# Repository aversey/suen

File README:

This board is the first implementation of SUEN architecture.

SUEN archictecture was created by Nikita Orlov and Aleksey Veresov
for research and educational purposes.

Board schematic was created with KiCad program complex.

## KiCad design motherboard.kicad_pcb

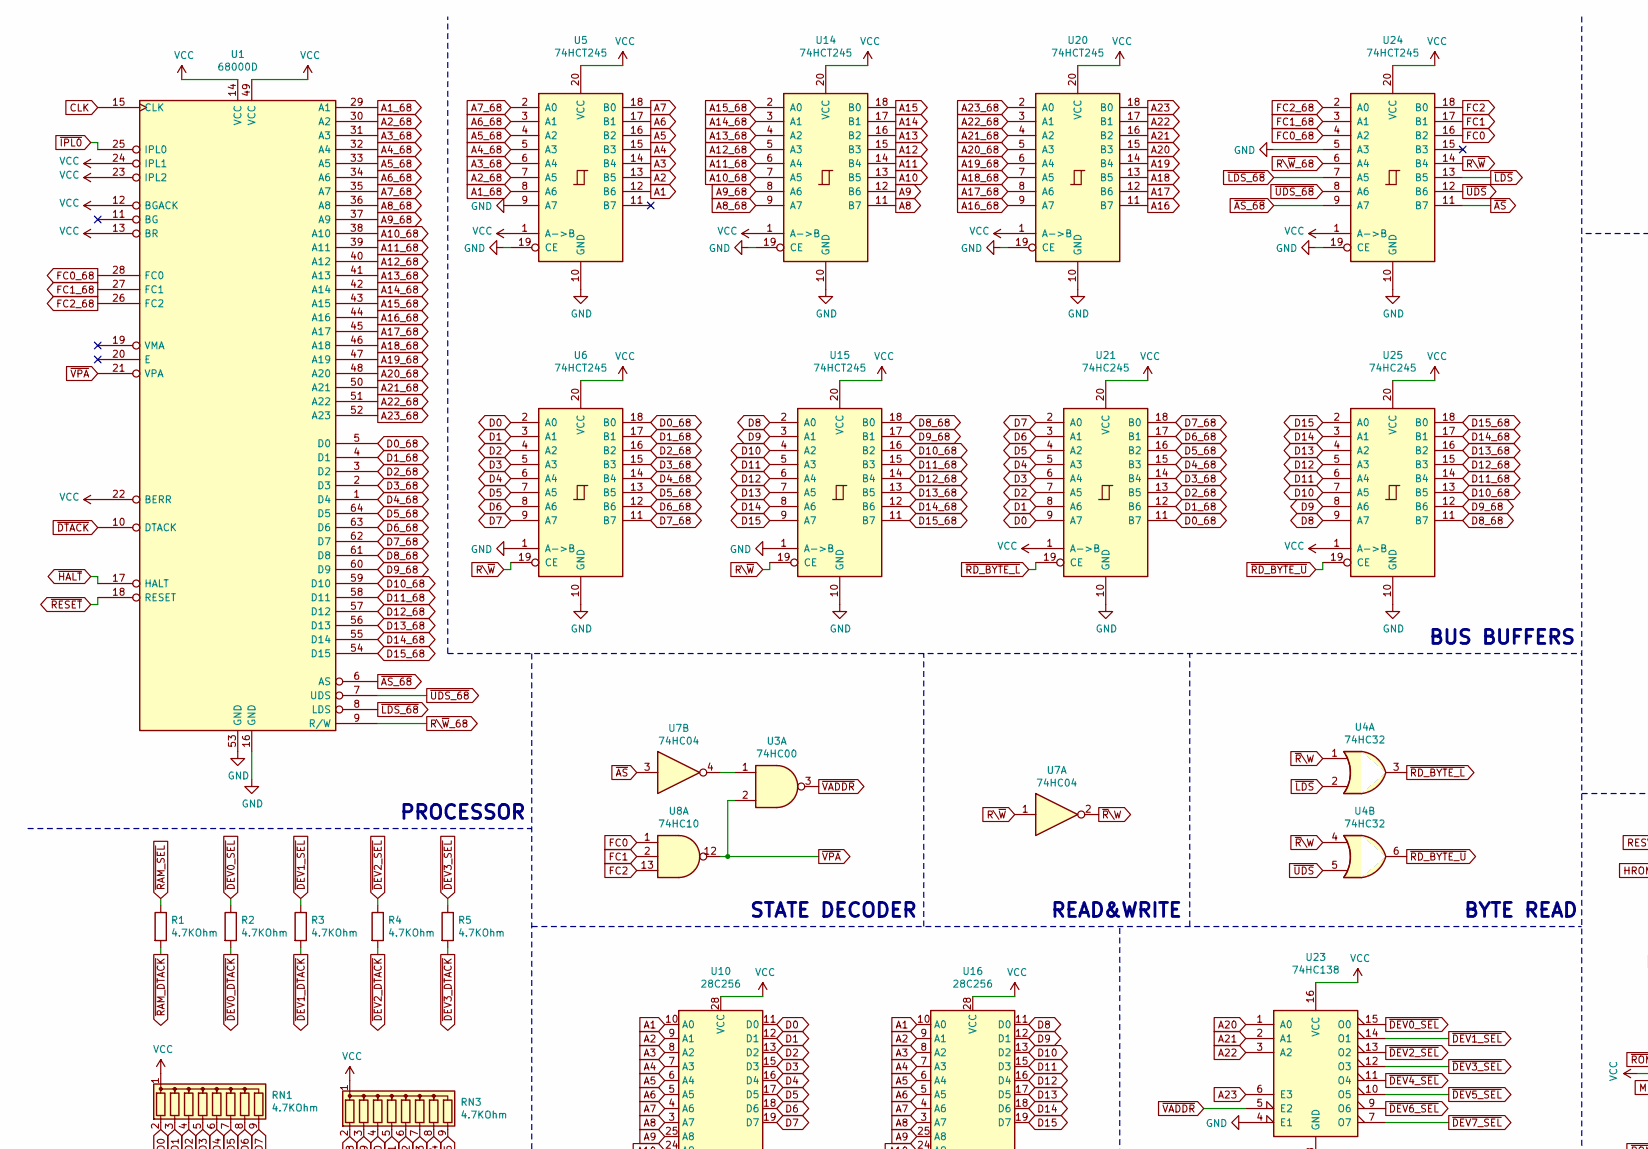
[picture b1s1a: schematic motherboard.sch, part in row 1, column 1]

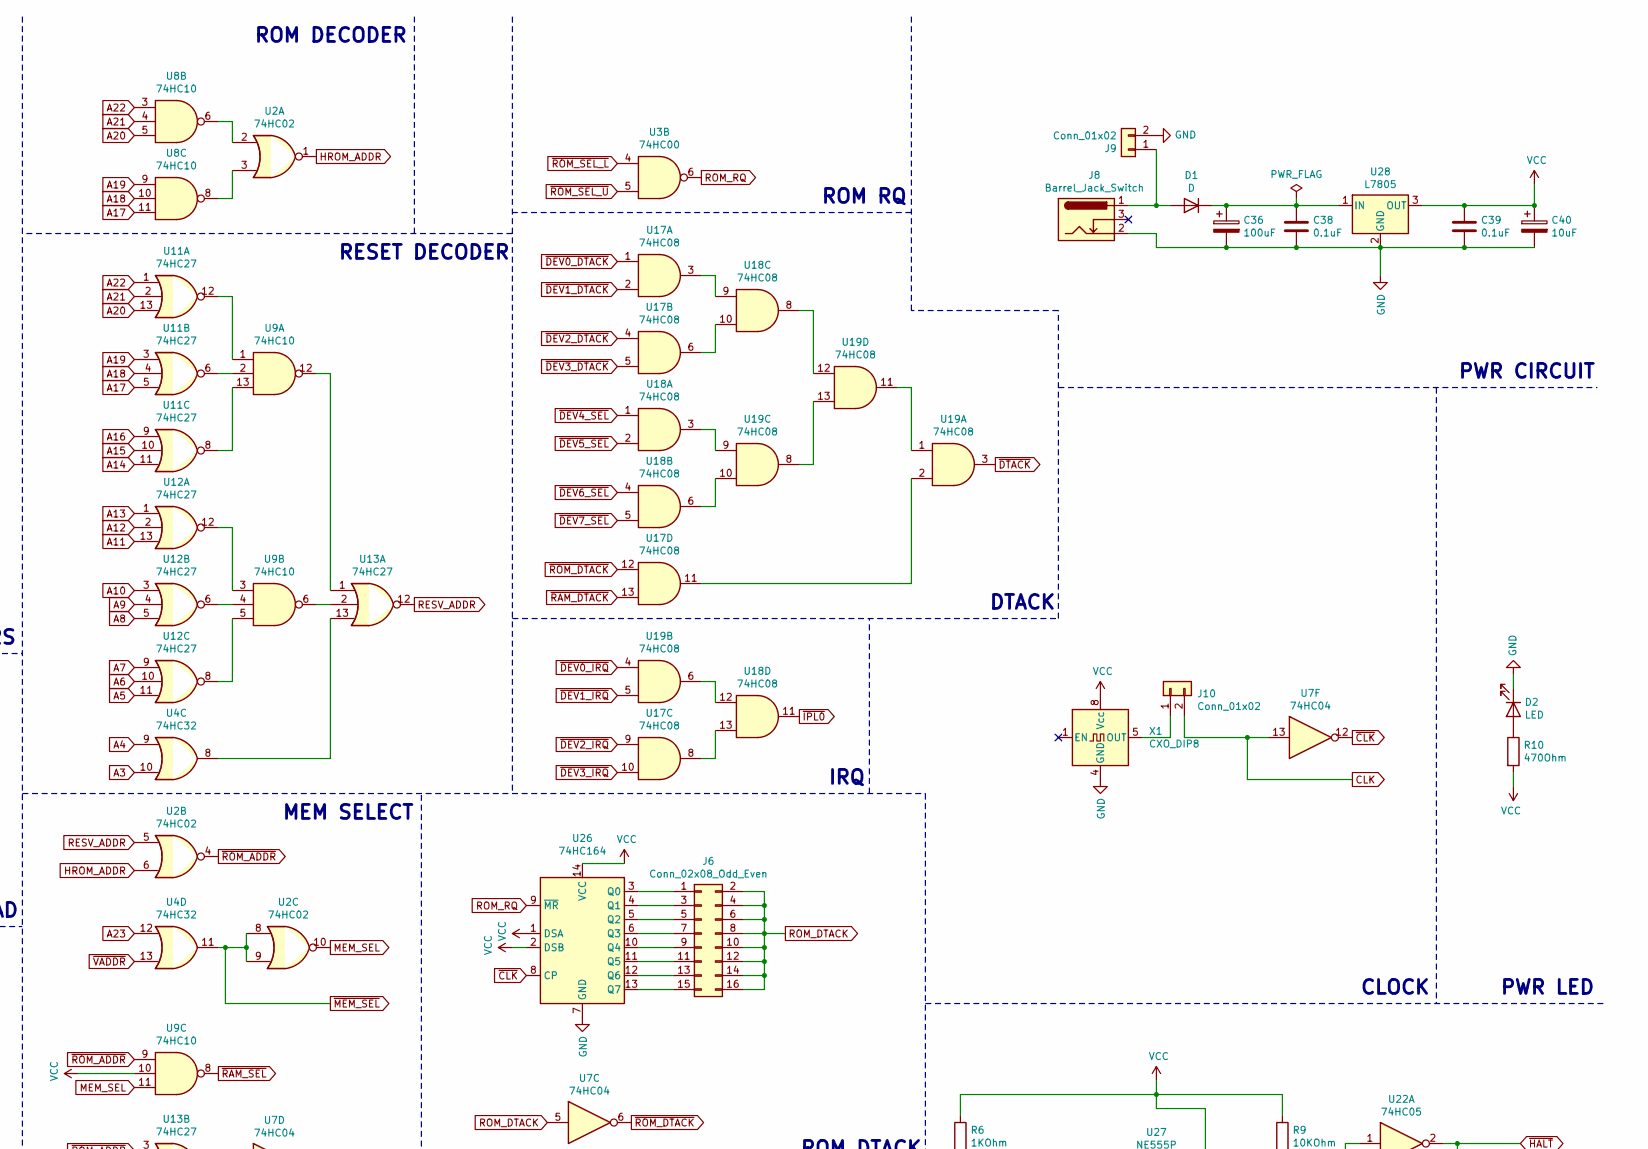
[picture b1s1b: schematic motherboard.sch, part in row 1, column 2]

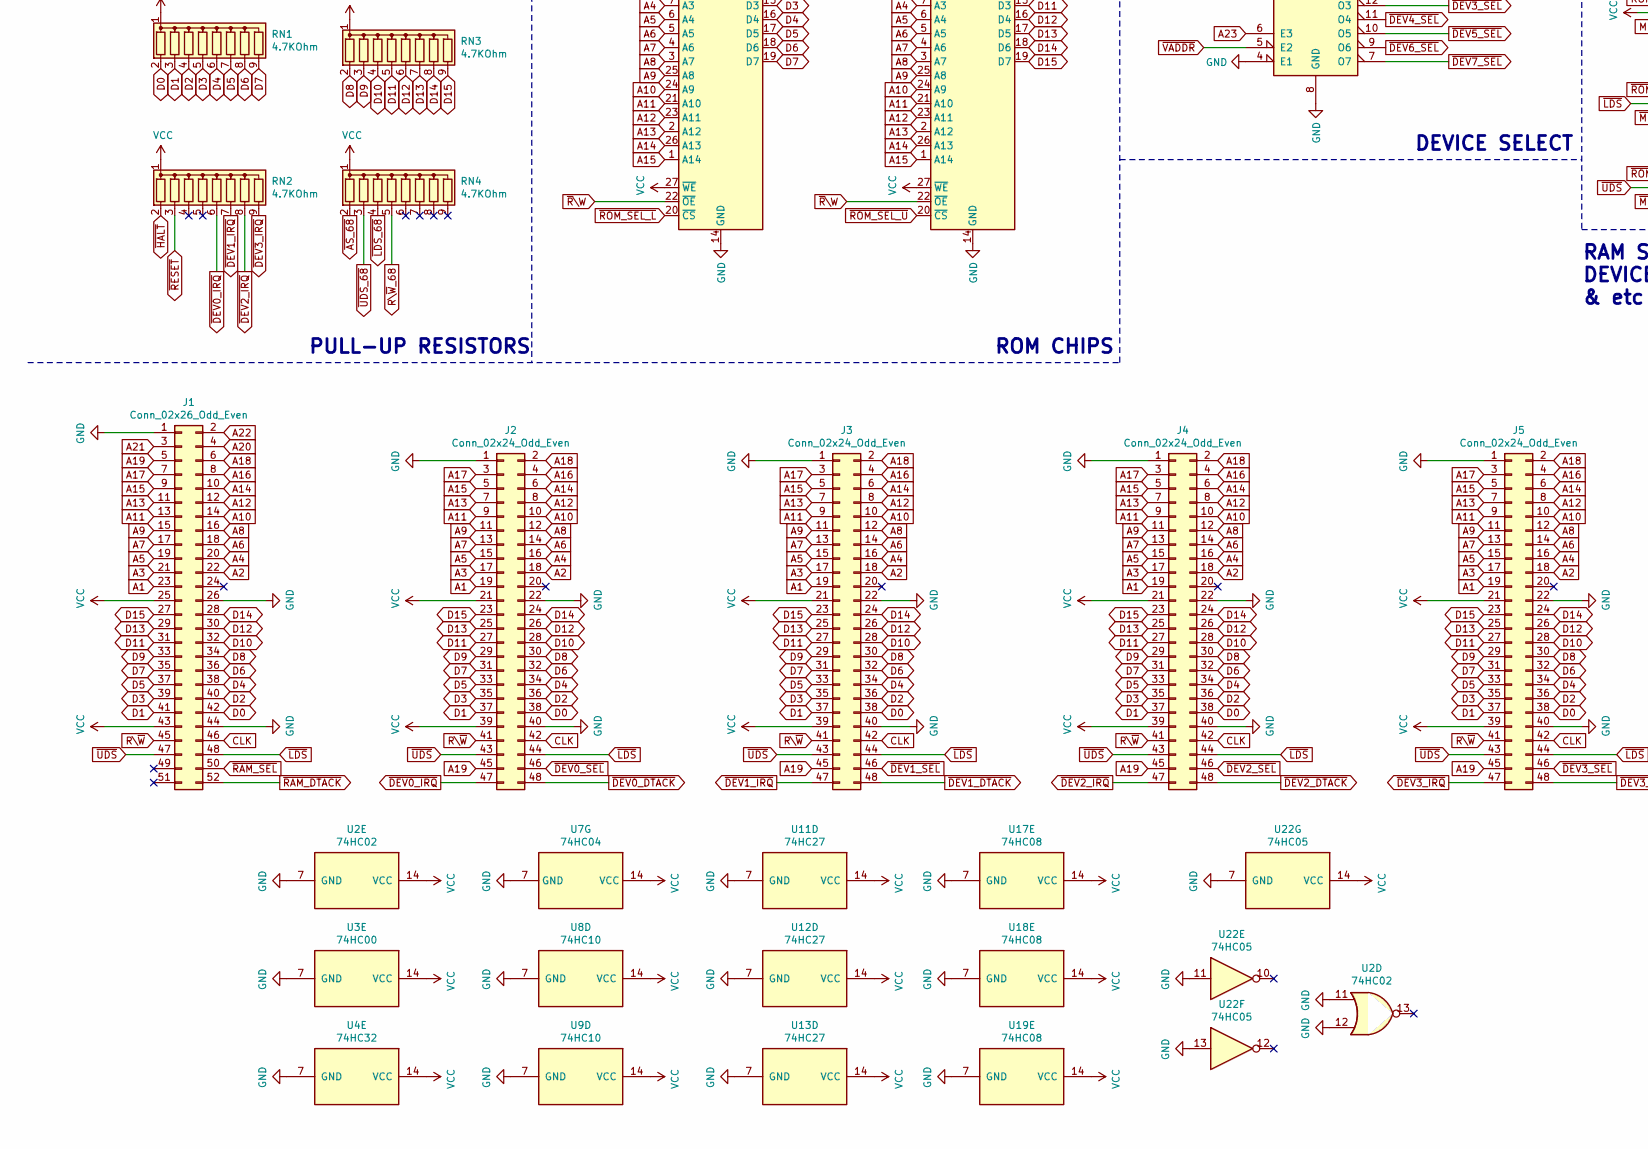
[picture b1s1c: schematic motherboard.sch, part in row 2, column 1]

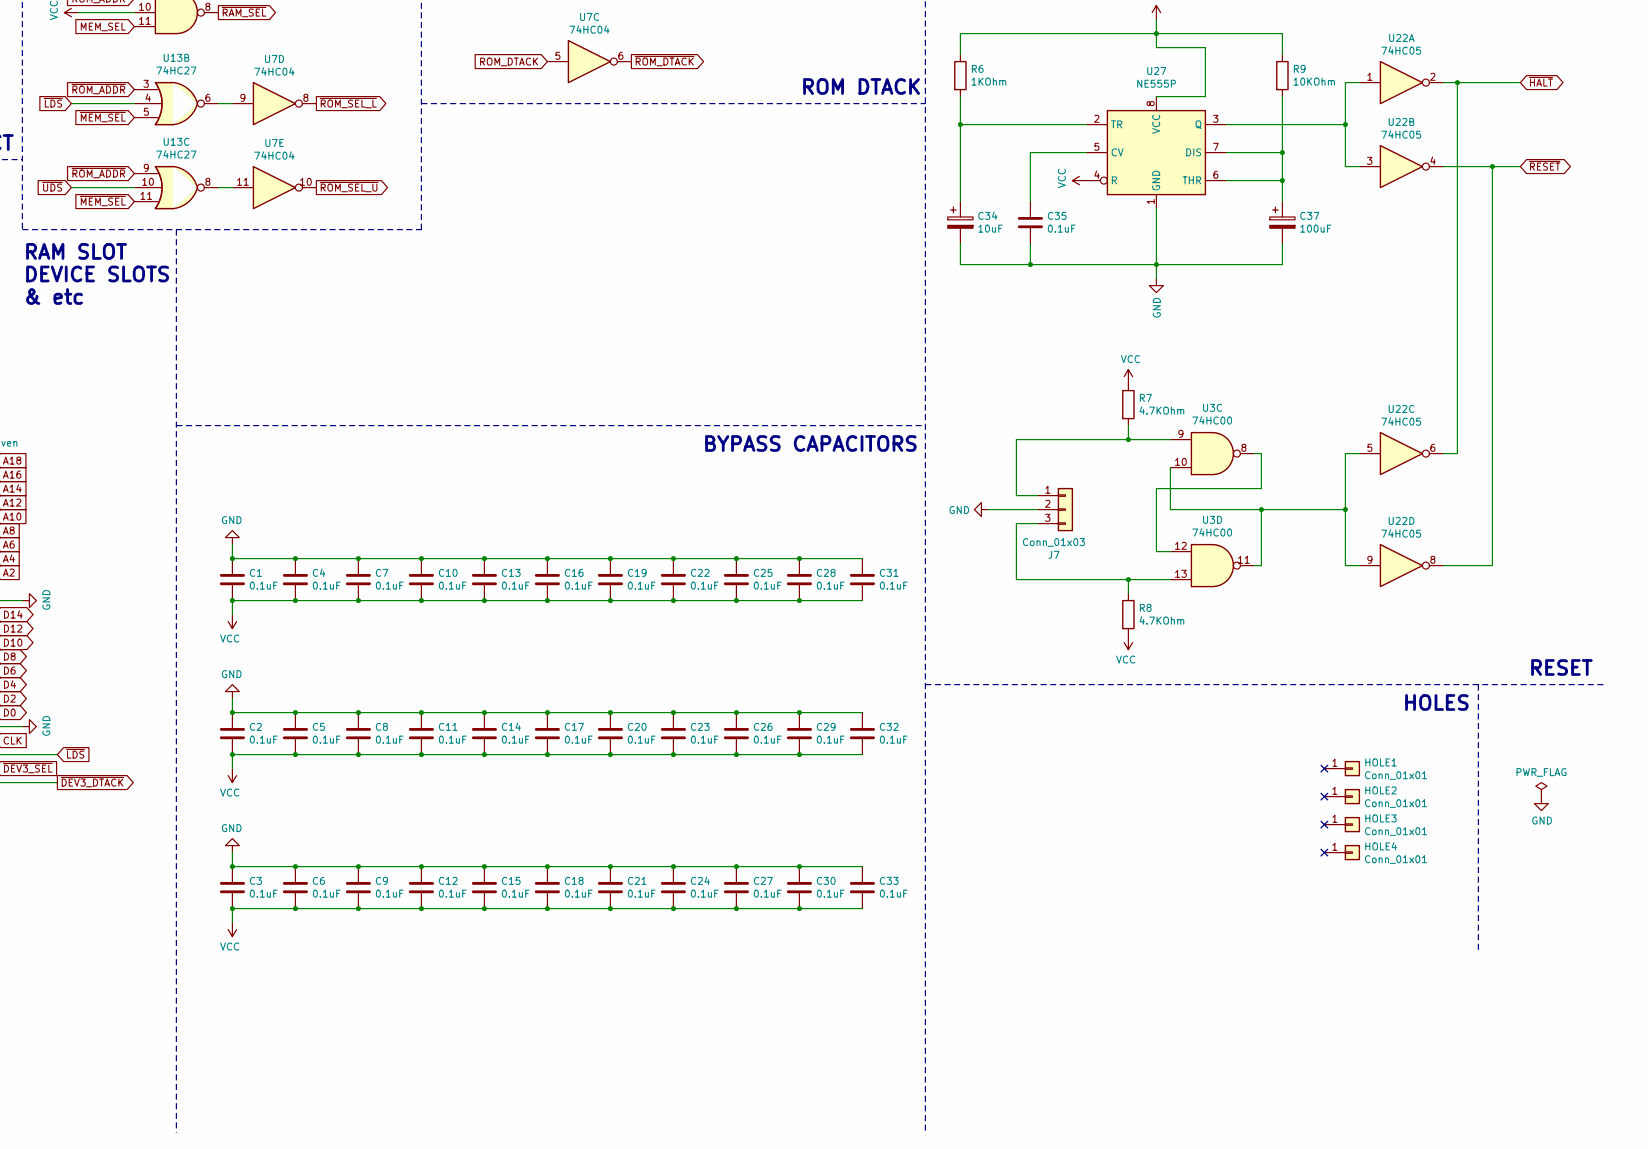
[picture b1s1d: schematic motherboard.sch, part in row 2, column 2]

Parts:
C1, C2, C3, C4, C5, C6, C7, C8, C9, C10, C11, C12, C13, C14, C15, C16, C17, C18, C19, C20, C21, C22, C23, C24, C25, C26, C27, C28, C29, C30, C31, C32, C33, C35, C38, C39: 0.1uF; C_Rect_L7.0mm_W4.5mm_P5.00mm
C34, C40: 10uF; CP_Radial_D4.0mm_P2.00mm
C36, C37: 100uF; CP_Radial_D5.0mm_P2.50mm
D1: D; D_DO-41_SOD81_P10.16mm_Horizontal
D2: LED; LED_D5.0mm
HOLE1, HOLE2, HOLE3, HOLE4: Conn_01x01; Hole
J1: Conn_02x26_Odd_Even; PinHeader_2x26_P2.54mm_Vertical
J2, J3, J4, J5: Conn_02x24_Odd_Even; PinHeader_2x24_P2.54mm_Vertical
J6: Conn_02x08_Odd_Even; PinHeader_2x08_P2.54mm_Vertical
J7: Conn_01x03; PinHeader_1x03_P2.54mm_Vertical
J8: Barrel_Jack_Switch; BarrelJack_Horizontal
J9, J10: Conn_01x02; PinHeader_1x02_P2.54mm_Vertical
R1, R2, R3, R4, R5, R7, R8: 4.7KOhm; R_Axial_DIN0414_L11.9mm_D4.5mm_P20.32mm_Horizontal
R6: 1KOhm; R_Axial_DIN0414_L11.9mm_D4.5mm_P20.32mm_Horizontal
R9: 10KOhm; R_Axial_DIN0414_L11.9mm_D4.5mm_P20.32mm_Horizontal
R10: 470Ohm; R_Axial_DIN0414_L11.9mm_D4.5mm_P20.32mm_Horizontal
RN1, RN2, RN3, RN4: 4.7KOhm; R_Array_SIP9
U1: 68000D; DIP-64_W22.86mm_Socket
U2: 74HC02; DIP-14_W7.62mm_Socket
U3: 74HC00; DIP-14_W7.62mm_Socket
U4: 74HC32; DIP-14_W7.62mm_Socket
U5, U6, U14, U15, U20, U24: 74HCT245; DIP-20_W7.62mm_Socket
U7: 74HC04; DIP-14_W7.62mm_Socket
U8, U9: 74HC10; DIP-14_W7.62mm_Socket
U10, U16: 28C256; DIP-28_W15.24mm_Socket
U11, U12, U13: 74HC27; DIP-14_W7.62mm_Socket
U17, U18, U19: 74HC08; DIP-14_W7.62mm_Socket
U21, U25: 74HC245; DIP-20_W7.62mm_Socket
U22: 74HC05; DIP-14_W7.62mm_Socket
U23: 74HC138; DIP-16_W7.62mm_Socket
U26: 74HC164; DIP-14_W7.62mm_Socket
U27: NE555P; DIP-8_W7.62mm_Socket
U28: L7805; TO-220-3_Horizontal_TabDown
X1: CXO_DIP8; Oscillator_DIP-8

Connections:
A1: J1.23, J2.19, J3.19, J4.19, J5.19, U5.12 (B6), U10.10 (A0), U16.10 (A0)
A1_68: U1.29 (A1), U5.8 (A6)
A2: J1.22, J2.18, J3.18, J4.18, J5.18, U5.13 (B5), U10.9 (A1), U16.9 (A1)
A2_68: U1.30 (A2), U5.7 (A5)
A3: J1.21, J2.17, J3.17, J4.17, J5.17, U4.10, U5.14 (B4), U10.8 (A2), U16.8 (A2)
A3_68: U1.31 (A3), U5.6 (A4)
A4: J1.20, J2.16, J3.16, J4.16, J5.16, U4.9, U5.15 (B3), U10.7 (A3), U16.7 (A3)
A4_68: U1.32 (A4), U5.5 (A3)
A5: J1.19, J2.15, J3.15, J4.15, J5.15, U5.16 (B2), U10.6 (A4), U12.11, U16.6 (A4)
A5_68: U1.33 (A5), U5.4 (A2)
A6: J1.18, J2.14, J3.14, J4.14, J5.14, U5.17 (B1), U10.5 (A5), U12.10, U16.5 (A5)
A6_68: U1.34 (A6), U5.3 (A1)
A7: J1.17, J2.13, J3.13, J4.13, J5.13, U5.18 (B0), U10.4 (A6), U12.9, U16.4 (A6)
A7_68: U1.35 (A7), U5.2 (A0)
A8: J1.16, J2.12, J3.12, J4.12, J5.12, U10.3 (A7), U12.5, U14.11 (B7), U16.3 (A7)
A8_68: U1.36 (A8), U14.9 (A7)
A9: J1.15, J2.11, J3.11, J4.11, J5.11, U10.25 (A8), U12.4, U14.12 (B6), U16.25 (A8)
A9_68: U1.37 (A9), U14.8 (A6)
A10: J1.14, J2.10, J3.10, J4.10, J5.10, U10.24 (A9), U12.3, U14.13 (B5), U16.24 (A9)
A10_68: U1.38 (A10), U14.7 (A5)
A11: J1.13, J2.9, J3.9, J4.9, J5.9, U10.21 (A10), U12.13, U14.14 (B4), U16.21 (A10)
A11_68: U1.39 (A11), U14.6 (A4)
A12: J1.12, J2.8, J3.8, J4.8, J5.8, U10.23 (A11), U12.2, U14.15 (B3), U16.23 (A11)
A12_68: U1.40 (A12), U14.5 (A3)
A13: J1.11, J2.7, J3.7, J4.7, J5.7, U10.2 (A12), U12.1, U14.16 (B2), U16.2 (A12)
A13_68: U1.41 (A13), U14.4 (A2)
A14: J1.10, J2.6, J3.6, J4.6, J5.6, U10.26 (A13), U11.11, U14.17 (B1), U16.26 (A13)
A14_68: U1.42 (A14), U14.3 (A1)
A15: J1.9, J2.5, J3.5, J4.5, J5.5, U10.1 (A14), U11.10, U14.18 (B0), U16.1 (A14)
A15_68: U1.43 (A15), U14.2 (A0)
A16: J1.8, J2.4, J3.4, J4.4, J5.4, U11.9, U20.11 (B7)
A16_68: U1.44 (A16), U20.9 (A7)
A17: J1.7, J2.3, J3.3, J4.3, J5.3, U8.11, U11.5, U20.12 (B6)
A17_68: U1.45 (A17), U20.8 (A6)
A18: J1.6, J2.2, J3.2, J4.2, J5.2, U8.10, U11.4, U20.13 (B5)
A18_68: U1.46 (A18), U20.7 (A5)
A19: J1.5, J2.45, J3.45, J4.45, J5.45, U8.9, U11.3, U20.14 (B4)
A19_68: U1.47 (A19), U20.6 (A4)
A20: J1.4, U8.5, U11.13, U20.15 (B3), U23.1 (A0)
A20_68: U1.48 (A20), U20.5 (A3)
A21: J1.3, U8.4, U11.2, U20.16 (B2), U23.2 (A1)
A21_68: U1.50 (A21), U20.4 (A2)
A22: J1.2, U8.3, U11.1, U20.17 (B1), U23.3 (A2)
A22_68: U1.51 (A22), U20.3 (A1)
A23: U4.12, U20.18 (B0), U23.6 (E3)
A23_68: U1.52 (A23), U20.2 (A0)
CLK: J1.46, J2.42, J3.42, J4.42, J5.42, J10.2, U1.15 (CLK), U7.13
D0: J1.42, J2.38, J3.38, J4.38, J5.38, RN1.2 (R1), U6.2 (A0), U10.11 (D0), U21.9 (A7)
D0_68: U1.5 (D0), U6.18 (B0), U21.11 (B7)
D1: J1.41, J2.37, J3.37, J4.37, J5.37, RN1.3 (R2), U6.3 (A1), U10.12 (D1), U21.8 (A6)
D1_68: U1.4 (D1), U6.17 (B1), U21.12 (B6)
D2: J1.40, J2.36, J3.36, J4.36, J5.36, RN1.4 (R3), U6.4 (A2), U10.13 (D2), U21.7 (A5)
D2_68: U1.3 (D2), U6.16 (B2), U21.13 (B5)
D3: J1.39, J2.35, J3.35, J4.35, J5.35, RN1.5 (R4), U6.5 (A3), U10.15 (D3), U21.6 (A4)
D3_68: U1.2 (D3), U6.15 (B3), U21.14 (B4)
D4: J1.38, J2.34, J3.34, J4.34, J5.34, RN1.6 (R5), U6.6 (A4), U10.16 (D4), U21.5 (A3)
D4_68: U1.1 (D4), U6.14 (B4), U21.15 (B3)
D5: J1.37, J2.33, J3.33, J4.33, J5.33, RN1.7 (R6), U6.7 (A5), U10.17 (D5), U21.4 (A2)
D5_68: U1.64 (D5), U6.13 (B5), U21.16 (B2)
D6: J1.36, J2.32, J3.32, J4.32, J5.32, RN1.8 (R7), U6.8 (A6), U10.18 (D6), U21.3 (A1)
D6_68: U1.63 (D6), U6.12 (B6), U21.17 (B1)
D7: J1.35, J2.31, J3.31, J4.31, J5.31, RN1.9 (R8), U6.9 (A7), U10.19 (D7), U21.2 (A0)
D7_68: U1.62 (D7), U6.11 (B7), U21.18 (B0)
D8: J1.34, J2.30, J3.30, J4.30, J5.30, RN3.2 (R1), U15.2 (A0), U16.11 (D0), U25.9 (A7)
D8_68: U1.61 (D8), U15.18 (B0), U25.11 (B7)
D9: J1.33, J2.29, J3.29, J4.29, J5.29, RN3.3 (R2), U15.3 (A1), U16.12 (D1), U25.8 (A6)
D9_68: U1.60 (D9), U15.17 (B1), U25.12 (B6)
D10: J1.32, J2.28, J3.28, J4.28, J5.28, RN3.4 (R3), U15.4 (A2), U16.13 (D2), U25.7 (A5)
D10_68: U1.59 (D10), U15.16 (B2), U25.13 (B5)
D11: J1.31, J2.27, J3.27, J4.27, J5.27, RN3.5 (R4), U15.5 (A3), U16.15 (D3), U25.6 (A4)
D11_68: U1.58 (D11), U15.15 (B3), U25.14 (B4)
D12: J1.30, J2.26, J3.26, J4.26, J5.26, RN3.6 (R5), U15.6 (A4), U16.16 (D4), U25.5 (A3)
D12_68: U1.57 (D12), U15.14 (B4), U25.15 (B3)
D13: J1.29, J2.25, J3.25, J4.25, J5.25, RN3.7 (R6), U15.7 (A5), U16.17 (D5), U25.4 (A2)
D13_68: U1.56 (D13), U15.13 (B5), U25.16 (B2)
D14: J1.28, J2.24, J3.24, J4.24, J5.24, RN3.8 (R7), U15.8 (A6), U16.18 (D6), U25.3 (A1)
D14_68: U1.55 (D14), U15.12 (B6), U25.17 (B1)
D15: J1.27, J2.23, J3.23, J4.23, J5.23, RN3.9 (R8), U15.9 (A7), U16.19 (D7), U25.2 (A0)
D15_68: U1.54 (D15), U15.11 (B7), U25.18 (B0)
FC0: U8.1, U24.16 (B2)
FC0_68: U1.28 (FC0), U24.4 (A2)
FC1: U8.2, U24.17 (B1)
FC1_68: U1.27 (FC1), U24.3 (A1)
FC2: U8.13, U24.18 (B0)
FC2_68: U1.26 (FC2), U24.2 (A0)
GND: C1.1, C2.1, C3.1, C4.1, C5.1, C6.1, C7.1, C8.1, C9.1, C10.1, C11.1, C12.1, C13.1, C14.1, C15.1, C16.1, C17.1, C18.1, C19.1, C20.1, C21.1, C22.1, C23.1, C24.1, C25.1, C26.1, C27.1, C28.1, C29.1, C30.1, C31.1, C32.1, C33.1, C34.2, C35.2, C36.2, C37.2, C38.2, C39.2, C40.2, D2.1 (K), J1.1, J1.26, J1.44, J2.1, J2.22, J2.40, J3.1, J3.22, J3.40, J4.1, J4.22, J4.40, J5.1, J5.22, J5.40, J7.2, J8.2, J9.2, U1.16 (GND), U1.53 (GND), U2.7 (GND), U2.11, U2.12, U3.7 (GND), U4.7 (GND), U5.9 (A7), U5.10 (GND), U5.19 (CE), U6.1 (A->B), U6.10 (GND), U7.7 (GND), U8.7 (GND), U9.7 (GND), U10.14 (GND), U11.7 (GND), U12.7 (GND), U13.7 (GND), U14.10 (GND), U14.19 (CE), U15.1 (A->B), U15.10 (GND), U16.14 (GND), U17.7 (GND), U18.7 (GND), U19.7 (GND), U20.10 (GND), U20.19 (CE), U21.10 (GND), U22.7 (GND), U22.11, U22.13, U23.4 (E1), U23.8 (GND), U24.5 (A3), U24.10 (GND), U24.19 (CE), U25.10 (GND), U26.7 (GND), U27.1 (GND), U28.2 (GND), X1.4 (GND)
HROM_ADDR: U2.1, U2.6
MEM_SEL: U2.10, U9.11
unnamed: C34.1, R6.2, U27.2 (TR)
unnamed: C35.1, U27.5 (CV)
unnamed: C36.1, C38.1, D1.1 (K), U28.1 (IN)
unnamed: C37.1, R9.2, U27.6 (THR), U27.7 (DIS)
unnamed: D1.2 (A), J8.1, J9.1
unnamed: D2.2 (A), R10.1
unnamed: J6.1, U26.3 (Q0)
unnamed: J6.3, U26.4 (Q1)
unnamed: J6.5, U26.5 (Q2)
unnamed: J6.7, U26.6 (Q3)
unnamed: J6.9, U26.10 (Q4)
unnamed: J6.11, U26.11 (Q5)
unnamed: J6.13, U26.12 (Q6)
unnamed: J6.15, U26.13 (Q7)
unnamed: J7.1, R7.2, U3.9
unnamed: J7.3, R8.1, U3.13
unnamed: J10.1, X1.5 (OUT)
unnamed: U2.2, U8.6
unnamed: U2.3, U8.8
unnamed: U3.1, U7.4
unnamed: U3.8, U3.12
unnamed: U9.2, U11.6
unnamed: U9.13, U11.8
unnamed: U9.1, U11.12
unnamed: U9.4, U12.6
unnamed: U9.5, U12.8
unnamed: U9.3, U12.12
unnamed: U9.12, U13.1
unnamed: U9.6, U13.2
unnamed: U7.9, U13.6
unnamed: U7.11, U13.8
unnamed: U4.8, U13.13
unnamed: U17.3, U18.9
unnamed: U17.6, U18.10
unnamed: U17.8, U18.13
unnamed: U17.11, U19.2
unnamed: U18.3, U19.9
unnamed: U18.6, U19.10
unnamed: U18.8, U19.12
unnamed: U18.12, U19.6
unnamed: U19.1, U19.11
unnamed: U19.8, U19.13
unnamed: U22.1, U22.3, U27.3 (Q)
unnamed: U3.10, U3.11, U22.5, U22.9
RESV_ADDR: U2.5, U13.12
ROM_DTACK: J6.2, J6.4, J6.6, J6.8, J6.10, J6.12, J6.14, J6.16, U7.5
ROM_RQ: U3.6, U26.9 (~MR)
R\~W: J1.45, J2.41, J3.41, J4.41, J5.41, U6.19 (CE), U7.1, U15.19 (CE), U24.14 (B4)
R\~W~_68: RN4.5 (R4), U1.9 (R/W), U24.6 (A4)
VCC: C1.2, C2.2, C3.2, C4.2, C5.2, C6.2, C7.2, C8.2, C9.2, C10.2, C11.2, C12.2, C13.2, C14.2, C15.2, C16.2, C17.2, C18.2, C19.2, C20.2, C21.2, C22.2, C23.2, C24.2, C25.2, C26.2, C27.2, C28.2, C29.2, C30.2, C31.2, C32.2, C33.2, C39.1, C40.1, J1.25, J1.43, J2.21, J2.39, J3.21, J3.39, J4.21, J4.39, J5.21, J5.39, R6.1, R7.1, R8.2, R9.1, R10.2, RN1.1 (common), RN2.1 (common), RN3.1 (common), RN4.1 (common), U1.12 (BGACK), U1.13 (BR), U1.14 (VCC), U1.22 (BERR), U1.23 (IPL2), U1.24 (IPL1), U1.49 (VCC), U2.14 (VCC), U3.14 (VCC), U4.14 (VCC), U5.1 (A->B), U5.20 (VCC), U6.20 (VCC), U7.14 (VCC), U8.14 (VCC), U9.10, U9.14 (VCC), U10.27 (~WE), U10.28 (VCC), U11.14 (VCC), U12.14 (VCC), U13.14 (VCC), U14.1 (A->B), U14.20 (VCC), U15.20 (VCC), U16.27 (~WE), U16.28 (VCC), U17.14 (VCC), U18.14 (VCC), U19.14 (VCC), U20.1 (A->B), U20.20 (VCC), U21.1 (A->B), U21.20 (VCC), U22.14 (VCC), U23.16 (VCC), U24.1 (A->B), U24.20 (VCC), U25.1 (A->B), U25.20 (VCC), U26.1 (DSA), U26.2 (DSB), U26.14 (VCC), U27.4 (R), U27.8 (VCC), U28.3 (OUT), X1.8 (Vcc)
~AS: U7.3, U24.11 (B7)
~AS_68: RN4.2 (R1), U1.6 (AS), U24.9 (A7)
~CLK: U7.12, U26.8 (CP)
~DEV0_DTACK: J2.48, R2.2, U17.1
~DEV0_IRQ: J2.47, RN2.6 (R5), U19.4
~DEV0_SEL: J2.46, R2.1, U23.15 (O0)
~DEV1_DTACK: J3.48, R3.2, U17.2
~DEV1_IRQ: J3.47, RN2.7 (R6), U19.5
~DEV1_SEL: J3.46, R3.1, U23.14 (O1)
~DEV2_DTACK: J4.48, R4.2, U17.4
~DEV2_IRQ: J4.47, RN2.8 (R7), U17.9
~DEV2_SEL: J4.46, R4.1, U23.13 (O2)
~DEV3_DTACK: J5.48, R5.2, U17.5
~DEV3_IRQ: J5.47, RN2.9 (R8), U17.10
~DEV3_SEL: J5.46, R5.1, U23.12 (O3)
~DEV4_SEL: U18.1, U23.11 (O4)
~DEV5_SEL: U18.2, U23.10 (O5)
~DEV6_SEL: U18.4, U23.9 (O6)
~DEV7_SEL: U18.5, U23.7 (O7)
~DTACK: U1.10 (DTACK), U19.3
~HALT: RN2.2 (R1), U1.17 (HALT), U22.2, U22.6
~IPL0: U1.25 (IPL0), U18.11
~LDS: J1.48, J2.44, J3.44, J4.44, J5.44, U4.2, U13.4, U24.13 (B5)
~LDS_68: RN4.4 (R3), U1.8 (LDS), U24.7 (A5)
~MEM_SEL: U2.8, U2.9, U4.11, U13.5, U13.11
~RAM_DTACK: J1.52, R1.2, U17.13
~RAM_SEL: J1.50, R1.1, U9.8
~RD_BYTE_L: U4.3, U21.19 (CE)
~RD_BYTE_U: U4.6, U25.19 (CE)
~RESET: RN2.3 (R2), U1.18 (RESET), U22.4, U22.8
~ROM_ADDR: U2.4, U9.9, U13.3, U13.9
~ROM_DTACK: U7.6, U17.12
~ROM_SEL_L: U3.4, U7.8, U10.20 (~CS)
~ROM_SEL_U: U3.5, U7.10, U16.20 (~CS)
~R~\W: U4.1, U4.4, U7.2, U10.22 (~OE), U16.22 (~OE)
~UDS: J1.47, J2.43, J3.43, J4.43, J5.43, U4.5, U13.10, U24.12 (B6)
~UDS_68: RN4.3 (R2), U1.7 (UDS), U24.8 (A6)
~VADDR: U3.3, U4.13, U23.5 (E2)
~VPA: U1.21 (VPA), U3.2, U8.12

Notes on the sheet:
CLOCK
PWR LED
RESET
HOLES
BYPASS CAPACITORS
IRQ
DTACK
ROM RQ
ROM DTACK
PWR CIRCUIT
MEM SELECT
RESET DECODER
ROM DECODER
RAM SLOT DEVICE SLOTS & etc
ROM CHIPS
DEVICE SELECT
PULL-UP RESISTORS
PROCESSOR
STATE DECODER
READ&WRITE
BYTE READ
BUS BUFFERS

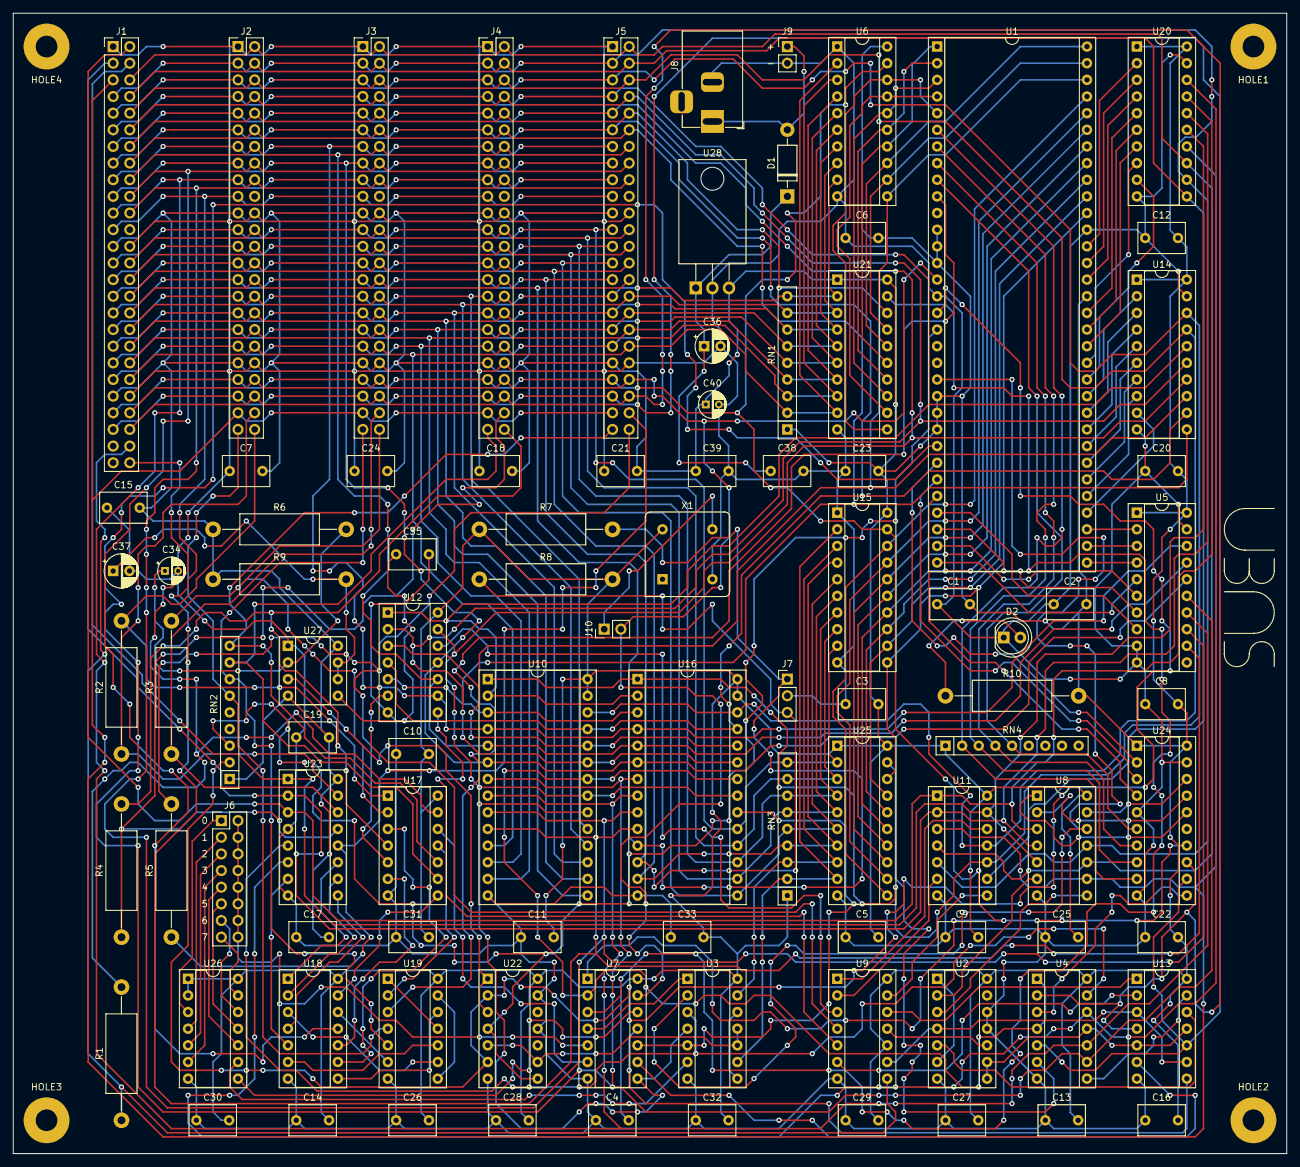
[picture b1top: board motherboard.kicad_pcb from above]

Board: 2 copper layers, 194.3 x 174.0 mm, 99 parts (0 on the bottom side), 177 nets.

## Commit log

2020-10-27 HC, HCT fix. Gerber archive removed. Scheme pdf added.
2020-12-04 Small gnd fix
2020-12-24 Description added
2020-12-29 555 timer update
2021-01-02 Gerber update
2021-01-16 Footrpint fix
2021-01-18 Trash removed
2021-01-18 More trash deleted, .gitignore added
2021-01-18 Motherboard schematic pdf update
2021-02-02 74HCT245 and bypass capacitors fix
